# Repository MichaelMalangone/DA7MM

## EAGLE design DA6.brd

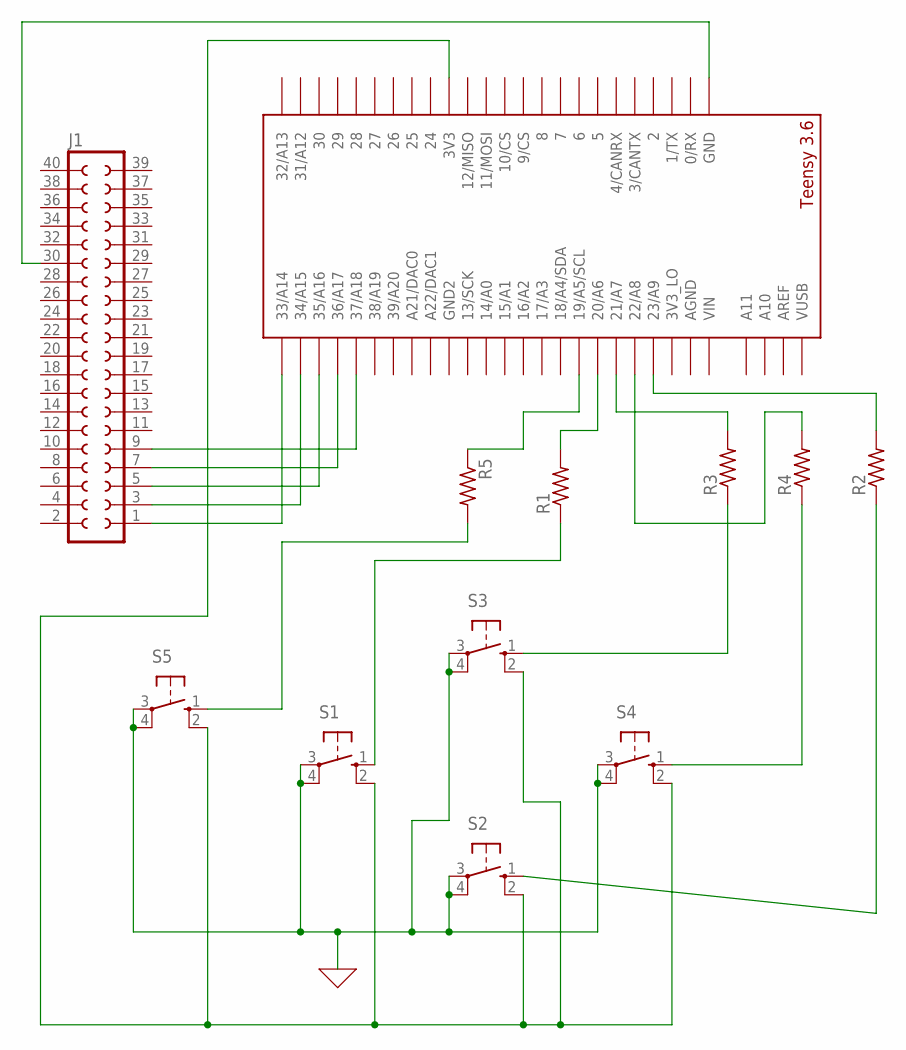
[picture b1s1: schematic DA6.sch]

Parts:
J1: SOCKET-40V; S40V
R1, R2, R3, R4, R5: R-US_0204/2V; 0204V
S1, S2, S3, S4, S5: 10-XX; B3F-10XX
U$1: TEENSY_3.5/3.6_BASIC

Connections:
0: S1.3, S1.4 (P1), S2.3, S2.4 (P1), S3.3, S3.4 (P1), S4.3, S4.4 (P1), S5.3, S5.4 (P1)
unnamed: J1.1, U$1.33/A14
unnamed: J1.3, U$1.34/A15
unnamed: J1.5, U$1.35/A16
unnamed: J1.7, U$1.36/A17
unnamed: J1.9, U$1.37/A18
unnamed: S1.2 (S1), S2.2 (S1), S3.2 (S1), S4.2 (S1), S5.2 (S1), U$1.3V3
unnamed: J1.30, U$1.GND
unnamed: R5.2, S5.1 (S)
unnamed: R5.1, U$1.19/A5/SCL
unnamed: R1.1, S1.1 (S)
unnamed: R3.1, S3.1 (S)
unnamed: R4.1, S4.1 (S)
unnamed: R2.1, S2.1 (S)
unnamed: R1.2, U$1.20/A6
unnamed: R3.2, U$1.21/A7
unnamed: R4.2, U$1.22/A8
unnamed: R2.2, U$1.23/A9

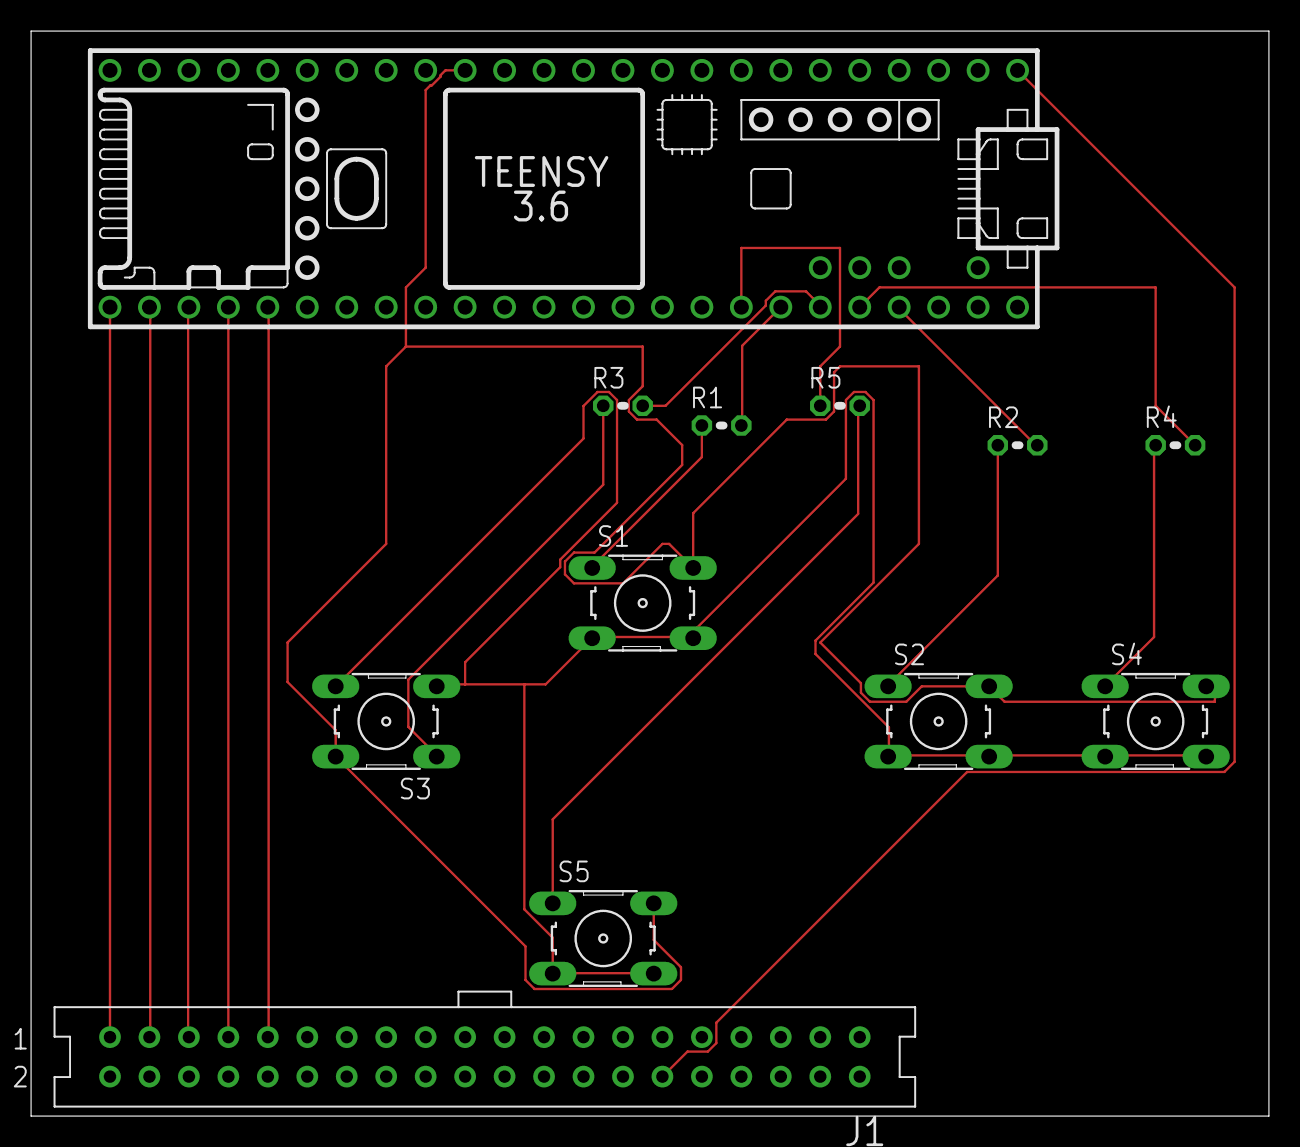
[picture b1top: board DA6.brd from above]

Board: 2 copper layers, 79.7 x 69.8 mm, 12 parts (0 on the bottom side), 18 nets.
